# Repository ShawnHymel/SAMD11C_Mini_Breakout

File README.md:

SparkFun SAMD11C14 Mini Breakout
========================================

[*SparkFun SAMD21 Mini Breakout (DEV-13664)*](https://www.sparkfun.com/products/13664)

The SAMD21 Mini Breakout is a [Pro Mini](https://www.sparkfun.com/products/11114)-sized breakout for the Atmel [ATSAMD21G18](http://www.atmel.com/devices/ATSAMD21G18.aspx), a 32-bit ARM Cortex-M0+ processor with 256KB flash, 32KB SRAM, and an operating speed of up to 48MHz. The SAMD21 is compatible with the Arduino IDE, and libraries for the Arduino Zero.

Repository Contents
-------------------

* **/Documentation** - Data sheets, additional product information
* **/Firmware** - SAMD21 Arduino Bootloader
* **/Hardware** - Eagle design files (.brd, .sch)
* **/Production** - Production panel files (.brd)

Documentation
--------------
* **[Hookup Guide](https://learn.sparkfun.com/tutorials/samd21-minidev-breakout-hookup-guide/resources--going-further)** - Basic hookup guide for the SAMD21 Mini Breakout.

Product Versions
----------------
* [DEV-13664](https://www.sparkfun.com/products/13664) - Initial product release - v10.
* [DEV-13672](https://www.sparkfun.com/products/13672) - The SparkFun SAMD21 _Dev_ Breakout -- a similar, Arduino-shaped version of this board.

Version History
---------------
* [v1.0](https://github.com/sparkfun/SAMD21G_Mini_Breakout/tree/v10) - Initial release 

License Information
-------------------

This product is _**open source**_! 

Please review the LICENSE.md file for license information. 

If you have any questions or concerns on licensing, please contact techsupport@sparkfun.com.

Distributed as-is; no warranty is given.

- Your friends at SparkFun.

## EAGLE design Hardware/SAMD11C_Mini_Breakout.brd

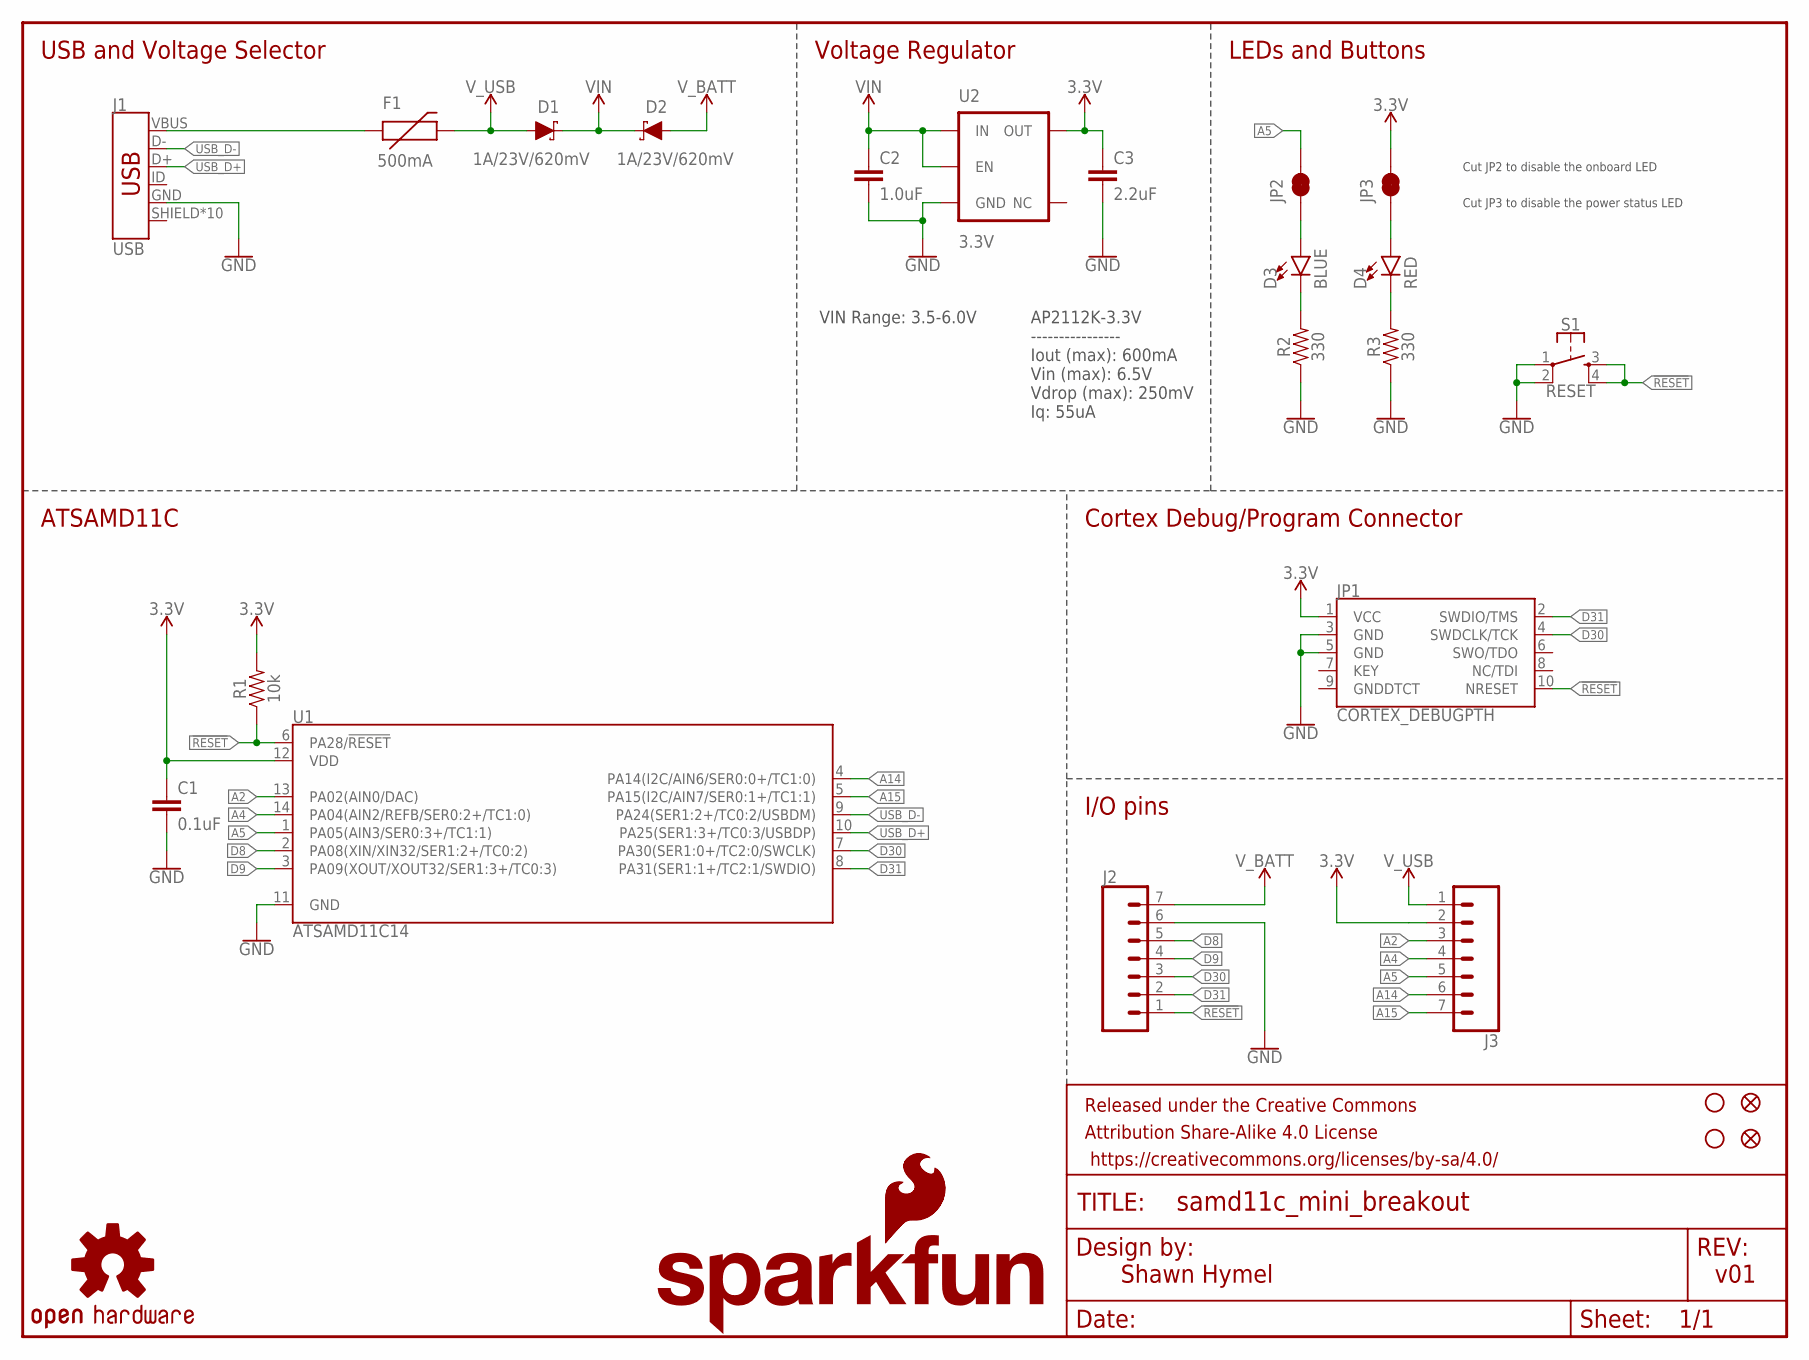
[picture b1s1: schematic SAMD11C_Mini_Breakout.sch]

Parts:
C1: 0.1uF; 0603
C2: 1.0uF; 0805
C3: 2.2uF; 0603
D1, D2: 1A/23V/620mV; SOD-323
D3: BLUE; LED-0603
D4: RED; LED-0603
F1: 500mA; PTC-1206
FD1, FD2: FIDUCIAL1X2; FIDUCIAL-1X2
FRAME1, FRAME2: FRAME-LETTER; CREATIVE_COMMONS
H3, H4: STAND-OFF
J1: USB; USB-MICROB-PTH-MILL
J2, J3: CONN_07NO_SILK; 1X07_NO_SILK
JP1: CORTEX_DEBUGPTH; 2X5-PTH-1.27MM
JP2, JP3: JUMPER-SMT_2_NC_TRACE_NO-SILK; SMT-JUMPER_2_NC_TRACE_NO-SILK
LOGO1: OSHW-LOGOS; OSHW-LOGO-S
LOGO2: SFE_LOGO_NAME_FLAME.1_INCH; SFE_LOGO_NAME_FLAME_.1
LOGO3: SFE_LOGO_FLAME.1_INCH; SFE_LOGO_FLAME_.1
R1: 10k; 0603
R2, R3: 330; 0603
S1: RESET; TACTILE_SWITCH_SMD_4.6X2.8MM
U1: ATSAMD11C14; SOIC-14
U2: 3.3V; SOT23-5

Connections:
3.3V: C1.1, C3.1, J3.2, JP1.1 (VCC), JP3.2, R1.2, U1.12 (VDD), U2.5 (OUT)
!RESET: J2.1, JP1.10 (NRESET), R1.1, S1.3, S1.4, U1.6 (PA28/!RESET!)
A2: J3.3, U1.13 (PA02(AIN0/DAC))
A4: J3.4, U1.14 (PA04(AIN2/REFB/SER0:2+/TC1:0))
A5: J3.5, JP2.2, U1.1 (PA05(AIN3/SER0:3+/TC1:1))
A14: J3.6, U1.4 (PA14(I2C/AIN6/SER0:0+/TC1:0))
A15: J3.7, U1.5 (PA15(I2C/AIN7/SER0:1+/TC1:1))
D8: J2.5, U1.2 (PA08(XIN/XIN32/SER1:2+/TC0:2))
D9: J2.4, U1.3 (PA09(XOUT/XOUT32/SER1:3+/TC0:3))
D30: J2.3, JP1.4 (SWDCLK/TCK), U1.7 (PA30(SER1:0+/TC2:0/SWCLK))
D31: J2.2, JP1.2 (SWDIO/TMS), U1.8 (PA31(SER1:1+/TC2:1/SWDIO))
GND: C1.2, C2.2, C3.2, J1.GND, J2.6, JP1.3 (GND), JP1.5 (GND), R2.1, R3.1, S1.1, S1.2, U1.11 (GND), U2.2 (GND)
unnamed: D3.A, JP2.1
unnamed: D3.C, R2.2
unnamed: D4.A, JP3.1
unnamed: F1.1, J1.VBUS
unnamed: D4.C, R3.2
USB_D+: J1.D+, U1.10 (PA25(SER1:3+/TC0:3/USBDP))
USB_D-: J1.D-, U1.9 (PA24(SER1:2+/TC0:2/USBDM))
VIN: C2.1, D1.C, D2.C, U2.1 (IN), U2.3 (EN)
V_BATT: D2.A, J2.7
V_USB: D1.A, F1.2, J3.1

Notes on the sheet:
Shawn Hymel
v01
VIN Range: 3.5-6.0V
AP2112K-3.3V ---------------- Iout (max): 600mA Vin (max): 6.5V Vdrop (max): 250mV Iq: 55uA
ATSAMD11C
USB and Voltage Selector
Voltage Regulator
LEDs and Buttons
Cortex Debug/Program Connector
I/O pins
Cut JP2 to disable the onboard LED
Cut JP3 to disable the power status LED

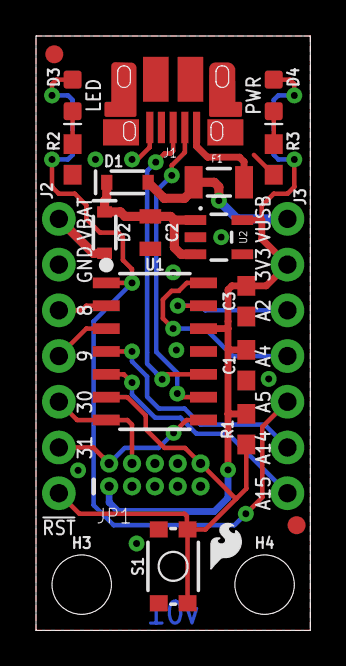
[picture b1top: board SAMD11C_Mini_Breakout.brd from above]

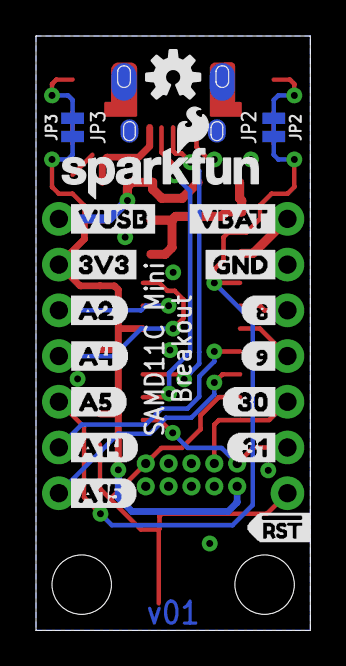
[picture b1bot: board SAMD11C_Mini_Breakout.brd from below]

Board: 2 copper layers, 15.2 x 33.0 mm, 43 parts (18 on the bottom side), 22 nets.

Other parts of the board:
U$1: #RST4
U$2: 3V33
U$3: 85
U$4: 96
U$5: 307
U$6: 318
U$7: A29
U$8: A410
U$9: A511
U$10: A1412
U$11: A1513
U$12: GND1
U$13: VBAT0
U$14: VUSB2

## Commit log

2018-08-15 Finished first draft of schematic
2018-08-18 Changed up schematic to have less parts. Moved parts on board around
2018-08-19 Finished layout for v01
2018-08-19 Removed duplicate schematic
2018-08-19 Renamed layout files to match repository
2018-08-19 Moved some labales around. Sent out for protos. v01.

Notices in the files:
parts and their libraries:
SparkFun-Capacitors: Licensing: Creative Commons ShareAlike 4.0 International - https://creativecommons.org/licenses/by-sa/4.0
SparkFun-DiscreteSemi: Licensing: CC v3.0 Share-Alike You are welcome to use this library for commercial purposes.
SparkFun-Aesthetics: Released under the Creative Commons
